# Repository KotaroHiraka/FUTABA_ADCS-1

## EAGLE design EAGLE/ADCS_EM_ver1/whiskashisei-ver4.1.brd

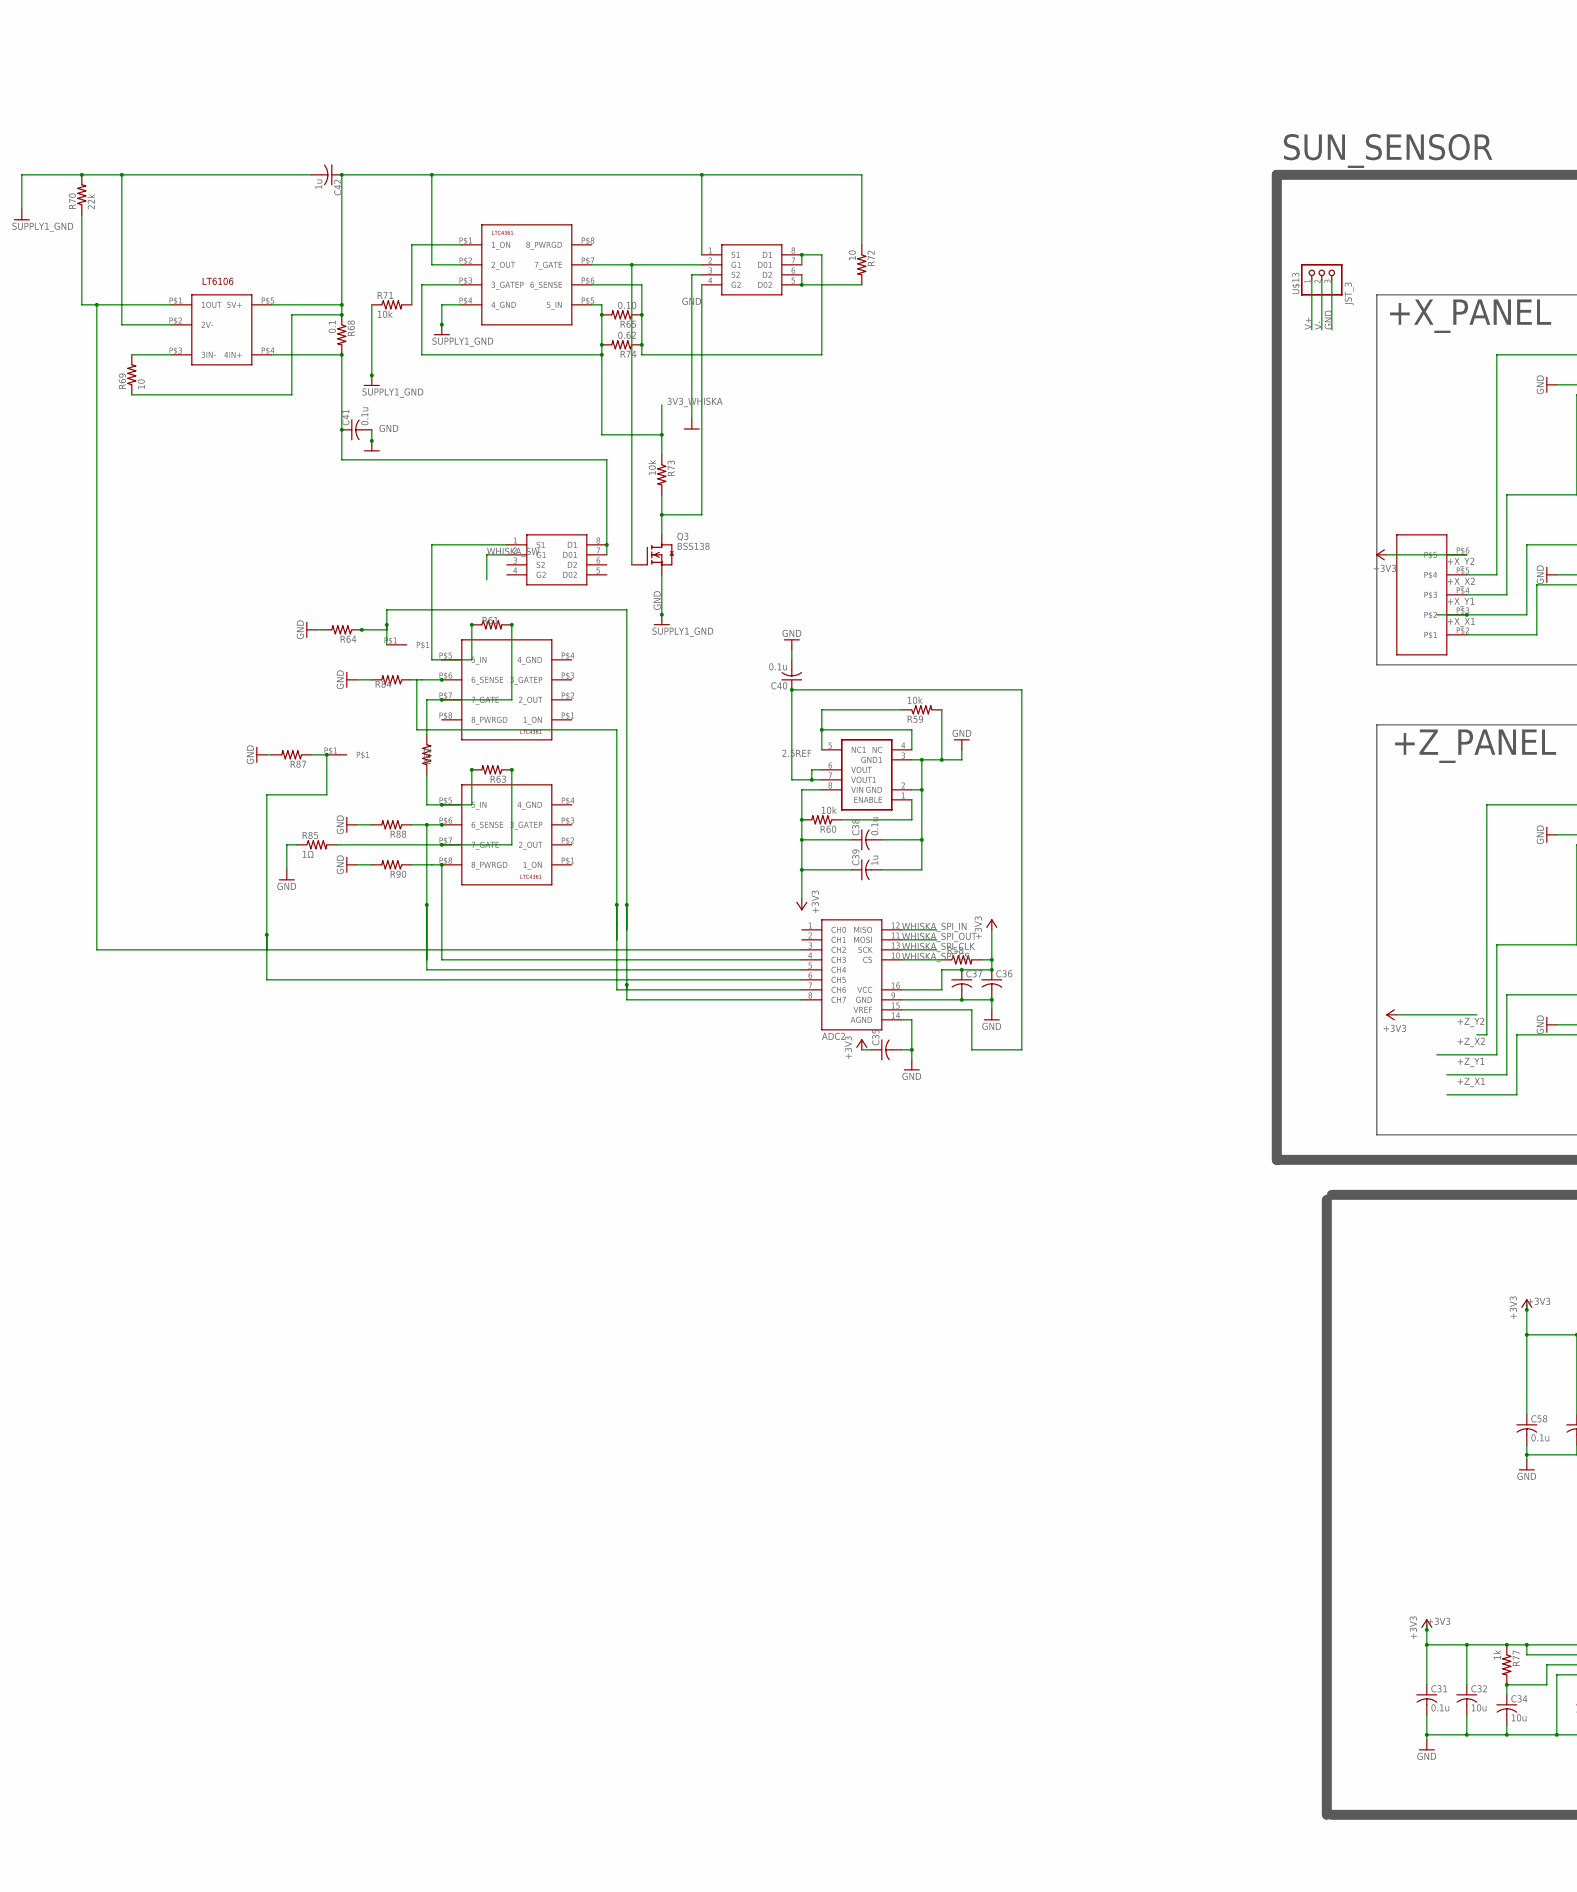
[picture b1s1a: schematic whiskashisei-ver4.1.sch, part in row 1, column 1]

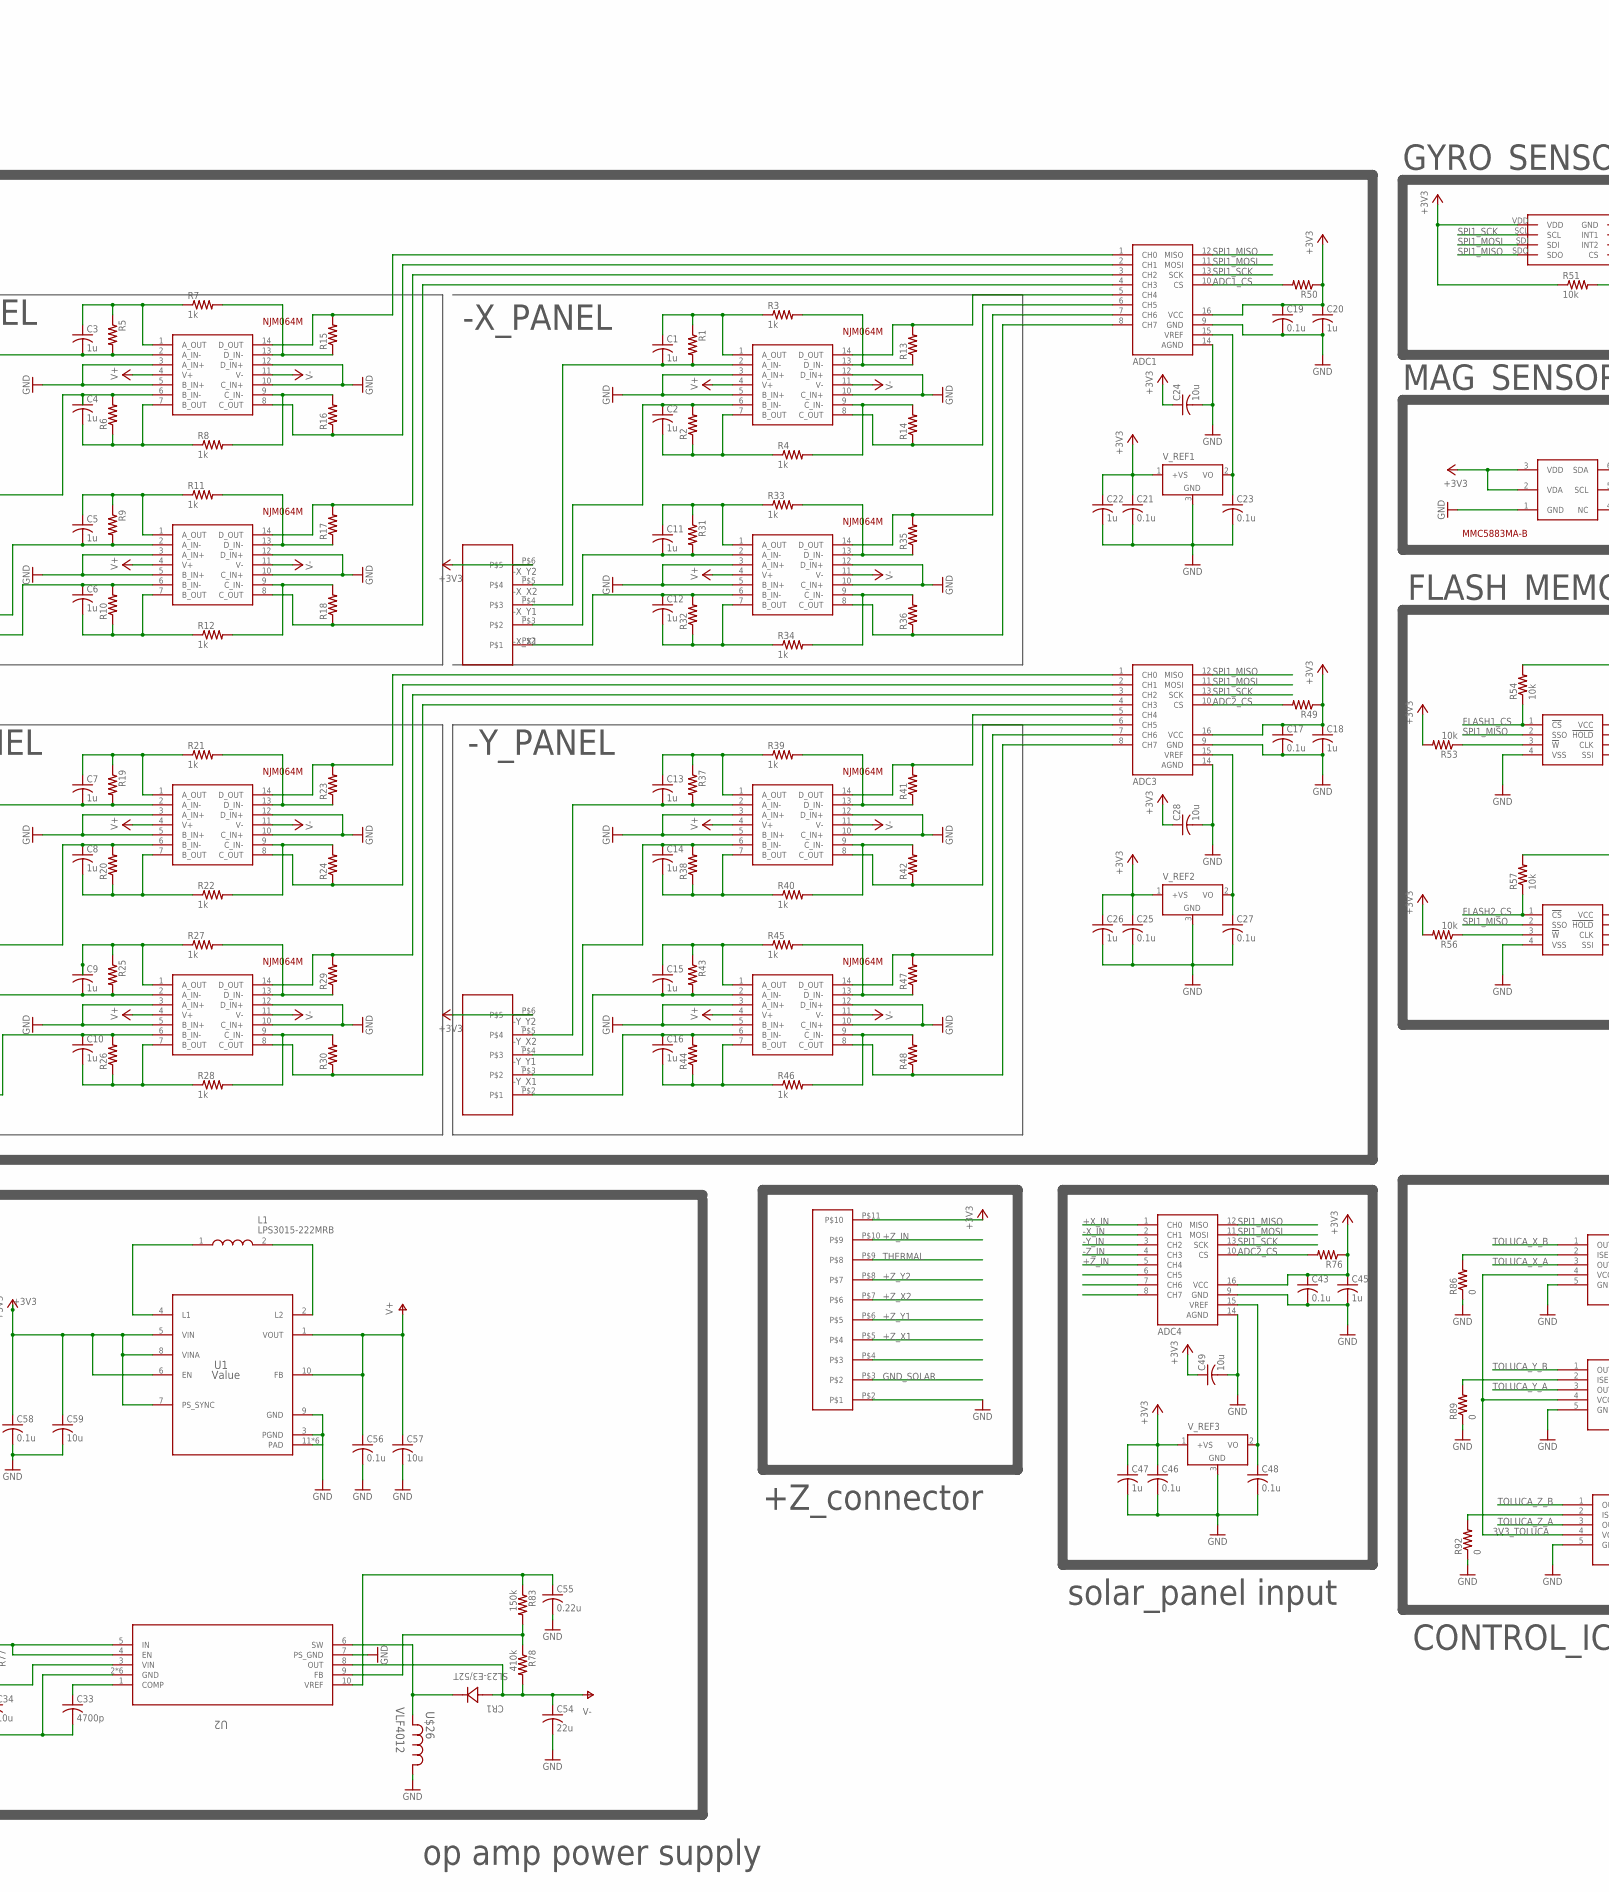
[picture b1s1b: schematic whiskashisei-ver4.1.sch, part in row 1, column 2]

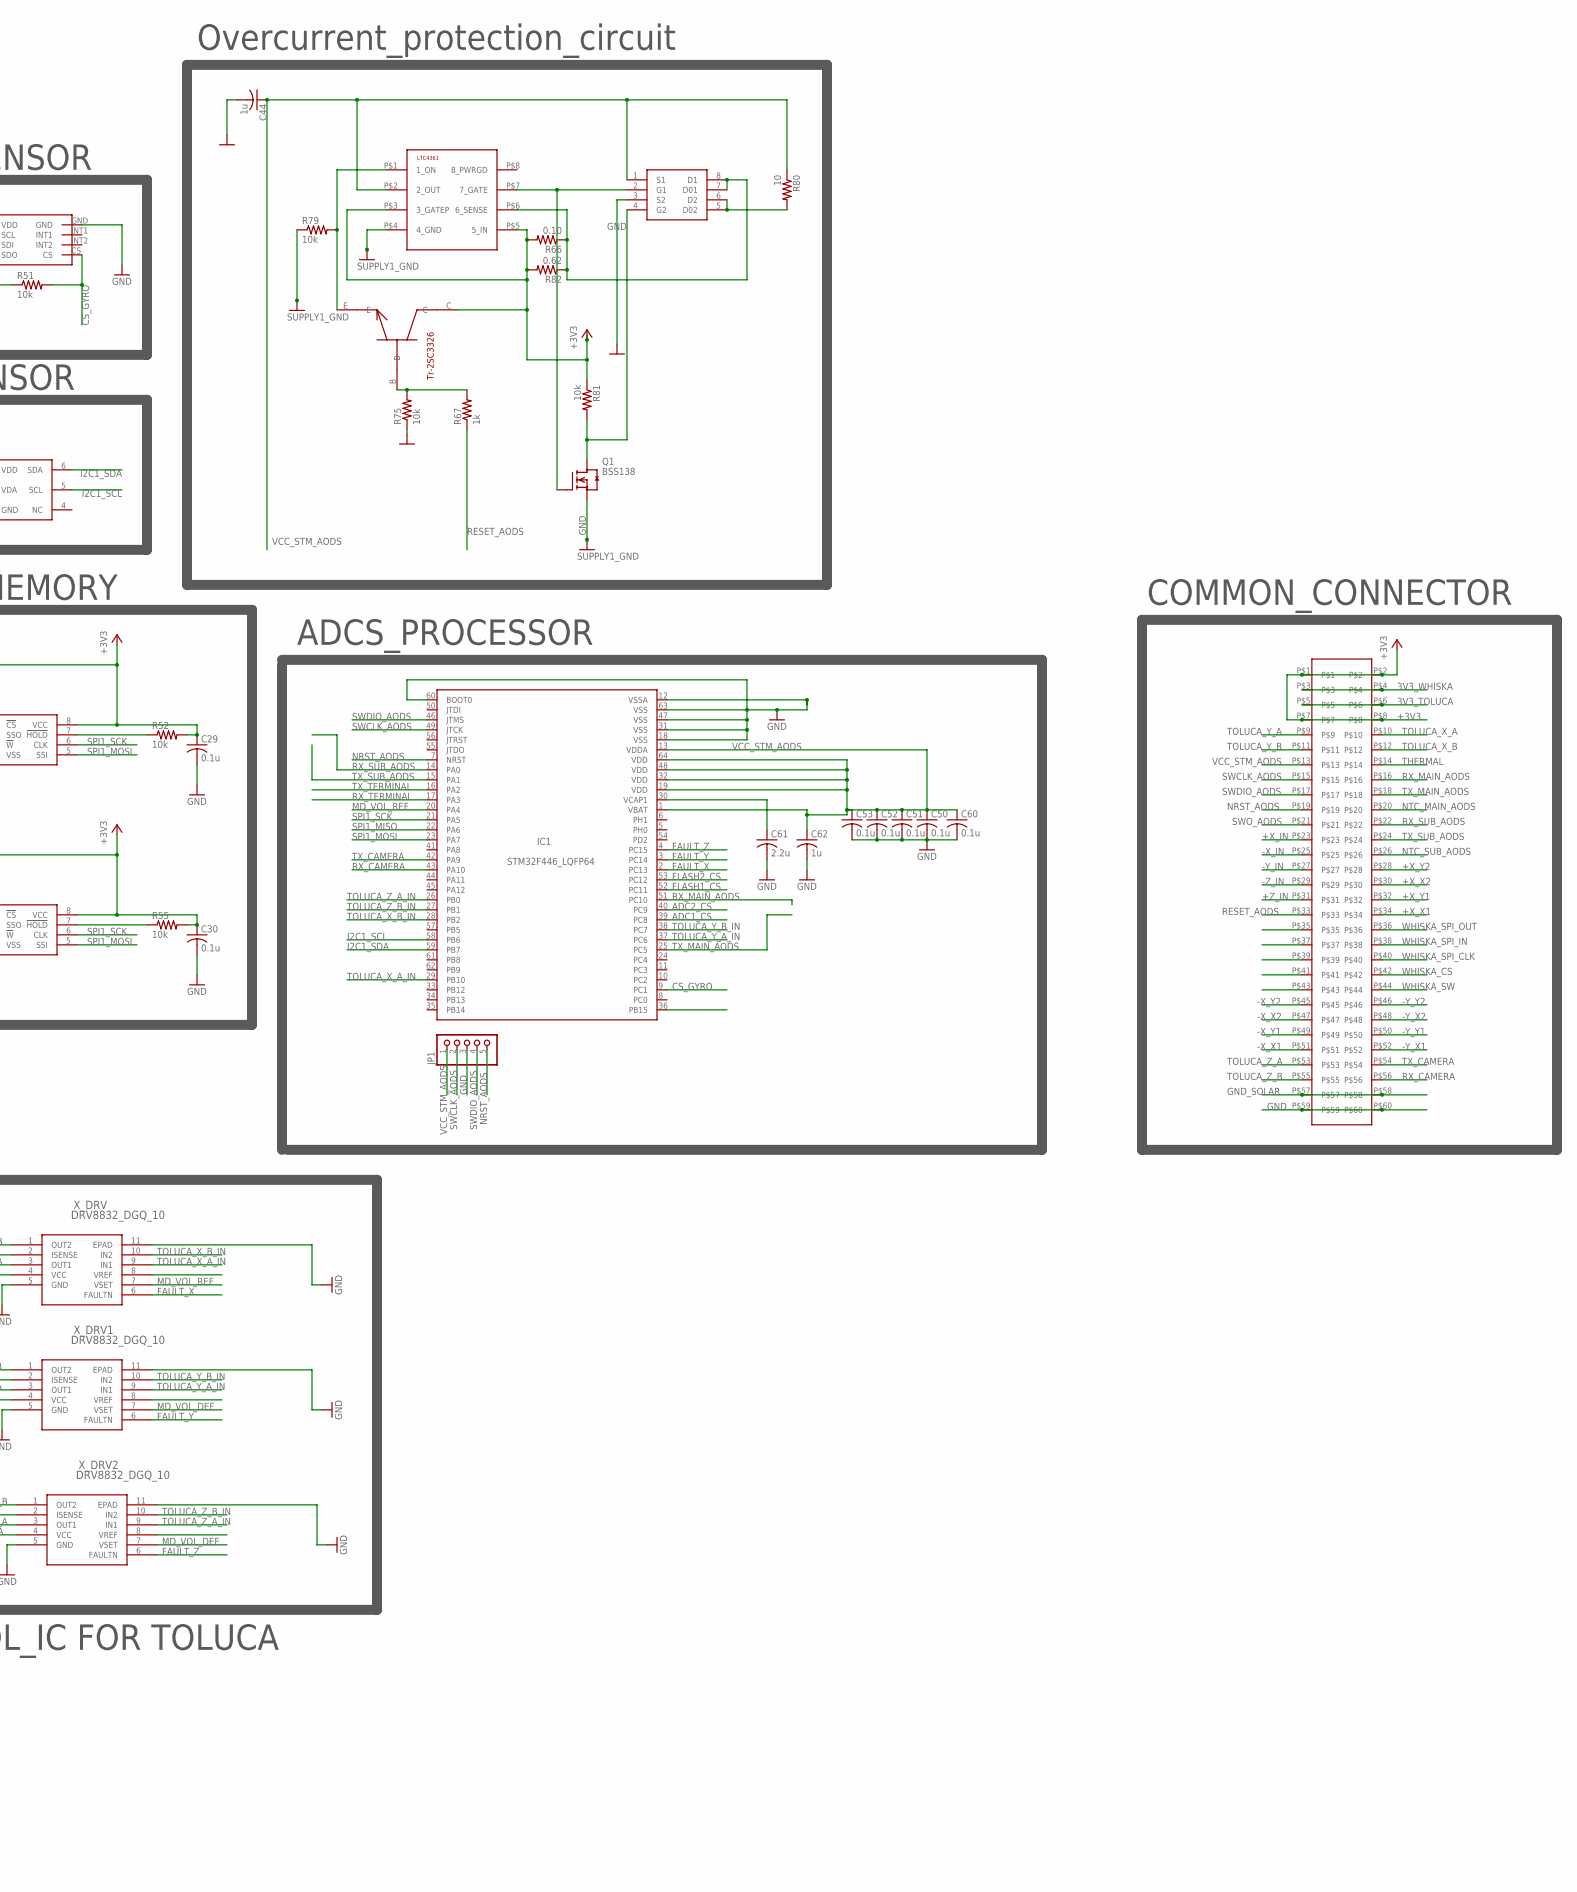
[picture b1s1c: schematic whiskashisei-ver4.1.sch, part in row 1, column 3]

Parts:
ADC1, ADC2, ADC3, ADC4: ADC_MCP3208; SO16
C1, C2, C3, C4, C5, C6, C7, C8, C9, C10, C11, C12, C13, C14, C15, C16, C18, C20, C22, C26, C39, C42, C44, C45, C47, C62: 1u; C2012
C17, C19, C21, C23, C25, C27, C29, C30, C31, C38, C40, C41, C43, C46, C48, C50, C51, C52, C53, C56, C58, C60: 0.1u; C2012
C24, C28, C32, C34, C49, C57, C59: 10u; C2012
C33: 4700p; C2012
C35, C36, C37: C-USC2012; C2012
C54: 22u; C2012
C55: 0.22u; C2012
C61: 2.2u; C2012
CR1: SL23-E3/52T; DIODE_DO214AA
FLASH_CAM: MP25P80; SO-08M
FLASH_SENSOR: MP25P80; SO-08M
IC1: STM32F446_LQFP64; LQFP64_PACKAGE
JP1: PINHD-1X5; 1X05
L1: LPS3015-222MRB; LPS3015
Q1, Q3: BSS138; SOT23
R1, R2, R5, R6, R9, R10, R13, R14, R15, R16, R17, R18, R19, R20, R23, R24, R25, R26, R29, R30, R31, R32, R35, R36, R37, R38, R41, R42, R43, R44, R47, R48, R49, R50, R58, R61, R62, R63, R64, R76, R84, R87, R88, R90: R-US_R2012; R2012
R3, R4, R7, R8, R11, R12, R21, R22, R27, R28, R33, R34, R39, R40, R45, R46, R67, R77: 1k; R2012
R51, R52, R53, R54, R55, R56, R57, R59, R60, R71, R73, R75, R79, R81: 10k; R2012
R65, R66: 0.10; R2012
R68: 0.1; R2012
R69, R72, R80: 10; R2012
R70: 22k; R2012
R74, R82: 0.62; R2012
R78: 410k; R2012
R83: 150k; R2012
R85: 1Ω; R2012
R86, R89, R92: 0; R2012
U1: Value; DRC0010A
U2: TPS63700DRCRG4; DRC10_2P4X1P65
U$1: 1.27_60
U$3: MMC5883MA-B
U$4: L3GD20_SET
U$5, U$6, U$7, U$8, U$9, U$10, U$11, U$12: NJM064M
U$13: JST_3
U$14: ADR3525
U$15, U$17, U$23, U$27: LTC4361; LTC4361_2
U$16, U$19, U$22: IRF7910; SO-08
U$18: LT6106
U$20: TR-NPN-2SC3326
U$21: JST_1MM_10
U$26: VLF4012; IND_4012
U$31, U$32, U$34: JST_1MM_5
V_REF1, V_REF2, V_REF3: LM50; SOT23
WHISKAPAD1, WHISKAPAD2: WHISKAPAD; LTC4361_2
X_DRV, X_DRV1, X_DRV2: DRV8832_DGQ_10; DGQ10_2P18X1P72

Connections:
2.5REF: ADC2.15 (VREF), C40.1, U$14.6 (VOUT), U$14.7 (VOUT1)
3V3_TOLUCA: U$1.P$5, U$1.P$6, X_DRV.4 (VCC), X_DRV1.4 (VCC), X_DRV2.4 (VCC)
3V3_WHISKA: R65.2, R73.1, R74.2, U$1.P$3, U$1.P$4, U$15.P$3 (3_GATEP), U$15.P$5 (5_IN)
+3V3: ADC1.16 (VCC), ADC2.16 (VCC), ADC3.16 (VCC), ADC4.16 (VCC), C17.1, C18.1, C19.1, C20.1, C21.1, C22.1, C24.1, C25.1, C26.1, C28.1, C29.1, C30.1, C31.1, C32.1, C35.1, C36.1, C37.1, C38.1, C39.1, C43.1, C45.1, C46.1, C47.1, C49.1, C58.1, C59.1, FLASH_CAM.8 (VCC), FLASH_SENSOR.8 (VCC), R49.1, R50.1, R51.1, R52.2, R53.2, R54.2, R55.2, R56.2, R57.2, R58.2, R60.2, R66.2, R76.1, R77.1, R81.1, R82.2, U1.5 (VIN), U1.6 (EN), U1.7 (PS_SYNC), U1.8 (VINA), U2.4 (EN), U2.5 (IN), U$1.P$1, U$1.P$2, U$1.P$7, U$1.P$8, U$3.2 (VDA), U$3.3 (VDD), U$4.VDD, U$14.8 (VIN), U$17.P$3 (3_GATEP), U$17.P$5 (5_IN), U$20.C, U$21.P$11, U$31.P$6, U$32.P$6, U$34.P$6, V_REF1.1 (+VS), V_REF2.1 (+VS), V_REF3.1 (+VS)
+X_IN: ADC4.1 (CH0), U$1.P$23
+X_X1: C6.1, R10.2, U$1.P$34, U$7.6 (B_IN-), U$31.P$2
+X_X2: C4.1, R6.2, U$1.P$30, U$6.6 (B_IN-), U$31.P$4
+X_Y1: C5.2, R9.2, U$1.P$32, U$7.2 (A_IN-), U$31.P$3
+X_Y2: C3.2, R5.2, U$1.P$28, U$6.2 (A_IN-), U$31.P$5
+Z_IN: ADC4.5 (CH4), U$1.P$31, U$21.P$10
+Z_X1: C10.1, R26.2, U$9.6 (B_IN-), U$21.P$5
+Z_X2: C8.1, R20.2, U$8.6 (B_IN-), U$21.P$7
+Z_Y1: C9.2, R25.2, U$9.2 (A_IN-), U$21.P$6
+Z_Y2: C7.2, R19.2, U$8.2 (A_IN-), U$21.P$8
-X_IN: ADC4.2 (CH1), U$1.P$25
-X_X1: C12.1, R32.2, U$1.P$51, U$10.6 (B_IN-), U$32.P$2
-X_X2: C2.1, R2.2, U$1.P$47, U$5.6 (B_IN-), U$32.P$4
-X_Y1: C11.2, R31.2, U$1.P$49, U$10.2 (A_IN-), U$32.P$3
-X_Y2: C1.2, R1.2, U$1.P$45, U$5.2 (A_IN-), U$32.P$5
-Y_IN: ADC4.3 (CH2), U$1.P$27
-Y_X1: C16.1, R44.2, U$1.P$52, U$12.6 (B_IN-), U$34.P$2
-Y_X2: C14.1, R38.2, U$1.P$48, U$11.6 (B_IN-), U$34.P$4
-Y_Y1: C15.2, R43.2, U$1.P$50, U$12.2 (A_IN-), U$34.P$3
-Y_Y2: C13.2, R37.2, U$1.P$46, U$11.2 (A_IN-), U$34.P$5
-Z_IN: ADC4.4 (CH3), U$1.P$29
ADC1_CS: ADC1.10 (CS), IC1.39 (PC8), R50.2
ADC2_CS: ADC3.10 (CS), ADC4.10 (CS), IC1.40 (PC9), R49.2, R76.2
CRT-18F: ADC2.3 (CH2), R70.1, U$18.P$1 (1OUT)
CS_GYRO: IC1.9 (PC1), R51.2, U$4.CS
FAULT_X: IC1.2 (PC13), X_DRV.6 (FAULTN)
FAULT_Y: IC1.3 (PC14), X_DRV1.6 (FAULTN)
FAULT_Z: IC1.4 (PC15), X_DRV2.6 (FAULTN)
FLASH1_CS: FLASH_SENSOR.1 (!CS), IC1.52 (PC11), R54.1
FLASH2_CS: FLASH_CAM.1 (!CS), IC1.53 (PC12), R57.1
G2: U$22.4 (G2)
GND: ADC1.9 (GND), ADC1.14 (AGND), ADC2.9 (GND), ADC2.14 (AGND), ADC3.9 (GND), ADC3.14 (AGND), ADC4.9 (GND), ADC4.14 (AGND), C17.2, C18.2, C19.2, C20.2, C21.2, C22.2, C23.2, C24.2, C25.2, C26.2, C27.2, C28.2, C29.2, C30.2, C31.2, C32.2, C33.2, C34.2, C35.2, C36.2, C37.2, C38.2, C39.2, C40.2, C41.2, C42.2, C43.2, C44.2, C45.2, C46.2, C47.2, C48.2, C49.2, C50.2, C51.2, C52.2, C53.2, C54.2, C55.2, C56.2, C57.2, C58.2, C59.2, C60.2, C61.2, C62.2, FLASH_CAM.4 (VSS), FLASH_SENSOR.4 (VSS), IC1.12 (VSSA), IC1.18 (VSS), IC1.31 (VSS), IC1.47 (VSS), IC1.60 (BOOT0), IC1.63 (VSS), JP1.3, Q1.2 (S), Q3.2 (S), R59.2, R64.2, R70.2, R71.1, R75.1, R79.1, R84.2, R85.1, R86.1, R87.2, R88.2, R89.1, R90.2, R92.1, U1.3 (PGND), U1.9 (GND), U1.11 (PAD), U1.P$1 (PAD), U1.P$2 (PAD), U1.P$3 (PAD), U1.P$4 (PAD), U1.V (PAD), U2.2 (GND), U2.7 (PS_GND), U2.11 (GND), U2.12 (GND), U2.13 (GND), U2.14 (GND), U2.15 (GND), U$1.P$59, U$1.P$60, U$3.1 (GND), U$4.GND, U$5.3 (A_IN+), U$5.5 (B_IN+), U$5.10 (C_IN+), U$5.12 (D_IN+), U$6.3 (A_IN+), U$6.5 (B_IN+), U$6.10 (C_IN+), U$6.12 (D_IN+), U$7.3 (A_IN+), U$7.5 (B_IN+), U$7.10 (C_IN+), U$7.12 (D_IN+), U$8.3 (A_IN+), U$8.5 (B_IN+), U$8.10 (C_IN+), U$8.12 (D_IN+), U$9.3 (A_IN+), U$9.5 (B_IN+), U$9.10 (C_IN+), U$9.12 (D_IN+), U$10.3 (A_IN+), U$10.5 (B_IN+), U$10.10 (C_IN+), U$10.12 (D_IN+), U$11.3 (A_IN+), U$11.5 (B_IN+), U$11.10 (C_IN+), U$11.12 (D_IN+), U$12.3 (A_IN+), U$12.5 (B_IN+), U$12.10 (C_IN+), U$12.12 (D_IN+), U$13.3, U$14.2 (GND), U$14.3 (GND1), U$15.P$4 (4_GND), U$16.3 (S2), U$17.P$4 (4_GND), U$18.P$2 (2V-), U$19.3 (S2), U$21.P$2, U$26.1, V_REF1.3 (GND), V_REF2.3 (GND), V_REF3.3 (GND), X_DRV.5 (GND), X_DRV.11 (EPAD), X_DRV1.5 (GND), X_DRV1.11 (EPAD), X_DRV2.5 (GND), X_DRV2.11 (EPAD)
GND_SOLAR: U$1.P$57, U$1.P$58, U$21.P$3
I2C1_SCL: IC1.58 (PB6), U$3.5 (SCL)
I2C1_SDA: IC1.59 (PB7), U$3.6 (SDA)
MD_VOL_DEF: X_DRV1.7 (VSET), X_DRV2.7 (VSET)
MD_VOL_REF: IC1.20 (PA4), X_DRV.7 (VSET)
unnamed: C4.2, R6.1, R8.1, U$6.7 (B_OUT)
unnamed: ADC1.1 (CH0), R15.2, U$6.14 (D_OUT)
unnamed: ADC1.2 (CH1), R16.1, U$6.8 (C_OUT)
unnamed: ADC1.6 (CH5), R14.1, U$5.8 (C_OUT)
unnamed: R8.2, R16.2, U$6.9 (C_IN-)
unnamed: ADC1.7 (CH6), R35.2, U$10.14 (D_OUT)
unnamed: ADC1.8 (CH7), R36.1, U$10.8 (C_OUT)
unnamed: ADC1.5 (CH4), R13.2, U$5.14 (D_OUT)
unnamed: ADC3.1 (CH0), R23.2, U$8.14 (D_OUT)
unnamed: C2.2, R2.1, R4.1, U$5.7 (B_OUT)
unnamed: R4.2, R14.2, U$5.9 (C_IN-)
unnamed: C8.2, R20.1, R22.1, U$8.7 (B_OUT)
unnamed: C1.1, R1.1, R3.1, U$5.1 (A_OUT)
unnamed: R3.2, R13.1, U$5.13 (D_IN-)
unnamed: C33.1, U2.1 (COMP)
unnamed: C3.1, R5.1, R7.1, U$6.1 (A_OUT)
unnamed: R7.2, R15.1, U$6.13 (D_IN-)
unnamed: C6.2, R10.1, R12.1, U$7.7 (B_OUT)
unnamed: R12.2, R18.2, U$7.9 (C_IN-)
unnamed: C5.1, R9.1, R11.1, U$7.1 (A_OUT)
unnamed: R11.2, R17.1, U$7.13 (D_IN-)
unnamed: R61.1, U$22.1 (S1), U$23.P$5 (5_IN)
unnamed: ADC1.15 (VREF), C23.1, V_REF1.2 (VO)
unnamed: ADC1.4 (CH3), R18.1, U$7.8 (C_OUT)
unnamed: C12.2, R32.1, R34.1, U$10.7 (B_OUT)
unnamed: ADC1.3 (CH2), R17.2, U$7.14 (D_OUT)
unnamed: R22.2, R24.2, U$8.9 (C_IN-)
unnamed: C7.1, R19.1, R21.1, U$8.1 (A_OUT)
unnamed: R21.2, R23.1, U$8.13 (D_IN-)
unnamed: C10.2, R26.1, R28.1, U$9.7 (B_OUT)
unnamed: R28.2, R30.2, U$9.9 (C_IN-)
unnamed: C9.1, R25.1, R27.1, U$9.1 (A_OUT)
unnamed: R27.2, R29.1, U$9.13 (D_IN-)
unnamed: C55.1, R83.1, U2.10 (VREF)
unnamed: C34.1, R77.2, U2.3 (VIN)
unnamed: ADC3.3 (CH2), R29.2, U$9.14 (D_OUT)
unnamed: ADC3.4 (CH3), R30.1, U$9.8 (C_OUT)
unnamed: R61.2, R62.2, U$23.P$7 (7_GATE)
unnamed: ADC3.2 (CH1), R24.1, U$8.8 (C_OUT)
unnamed: R34.2, R36.2, U$10.9 (C_IN-)
unnamed: C11.1, R31.1, R33.1, U$10.1 (A_OUT)
unnamed: R33.2, R35.1, U$10.13 (D_IN-)
unnamed: ADC3.15 (VREF), C27.1, V_REF2.2 (VO)
unnamed: ADC3.5 (CH4), R41.2, U$11.14 (D_OUT)
unnamed: ADC3.6 (CH5), R42.1, U$11.8 (C_OUT)
unnamed: C14.2, R38.1, R40.1, U$11.7 (B_OUT)
unnamed: R40.2, R42.2, U$11.9 (C_IN-)
unnamed: C13.1, R37.1, R39.1, U$11.1 (A_OUT)
unnamed: R39.2, R41.1, U$11.13 (D_IN-)
unnamed: ADC4.15 (VREF), C48.1, V_REF3.2 (VO)
unnamed: C16.2, R44.1, R46.1, U$12.7 (B_OUT)
unnamed: R46.2, R48.2, U$12.9 (C_IN-)
unnamed: C15.1, R43.1, R45.1, U$12.1 (A_OUT)
unnamed: R45.2, R47.1, U$12.13 (D_IN-)
unnamed: R78.1, R83.2, U2.9 (FB)
unnamed: CR1.1, U2.6 (SW), U$26.2
unnamed: ADC3.7 (CH6), R47.2, U$12.14 (D_OUT)
unnamed: ADC3.8 (CH7), R48.1, U$12.8 (C_OUT)
unnamed: R65.1, R74.1, U$15.P$6 (6_SENSE), U$16.7 (D01), U$16.8 (D1)
unnamed: FLASH_SENSOR.3 (!W), R53.1
unnamed: FLASH_CAM.7 (!HOLD), R55.1
unnamed: Q3.1 (G), U$15.P$7 (7_GATE), U$16.2 (G1)
unnamed: FLASH_CAM.3 (!W), R56.1
unnamed: FLASH_SENSOR.7 (!HOLD), R52.1
unnamed: C42.1, R68.1, R69.1, R72.1, U$15.P$2 (2_OUT), U$16.1 (S1), U$18.P$5 (5V+)
unnamed: R89.2, X_DRV1.2 (ISENSE)
unnamed: R62.1, R63.2, U$27.P$5 (5_IN)
unnamed: L1.1, U1.4 (L1)
unnamed: L1.2, U1.2 (L2)
unnamed: R59.1, U$14.4 (NC), U$14.5 (NC1)
unnamed: R60.1, U$14.1 (ENABLE)
unnamed: R71.2, U$15.P$1 (1_ON)
unnamed: C41.1, R68.2, U$18.P$4 (4IN+), U$22.7 (D01), U$22.8 (D1)
unnamed: R69.2, U$18.P$3 (3IN-)
unnamed: R72.2, U$16.5 (D02), U$16.6 (D2)
unnamed: Q3.3 (D), R73.2, U$16.4 (G2)
unnamed: R66.1, R82.1, U$17.P$6 (6_SENSE), U$19.7 (D01), U$19.8 (D1)
unnamed: Q1.1 (G), U$17.P$7 (7_GATE), U$19.2 (G1)
unnamed: R79.2, U$17.P$1 (1_ON), U$20.E
unnamed: R67.2, R75.2, U$20.B
unnamed: R80.2, U$19.5 (D02), U$19.6 (D2)
unnamed: Q1.3 (D), R81.2, U$19.4 (G2)
unnamed: R92.2, X_DRV2.2 (ISENSE)
unnamed: ADC2.6 (CH5), R87.1, WHISKAPAD1.P$1
unnamed: ADC2.4 (CH3), R90.1, U$27.P$8 (8_PWRGD)
unnamed: ADC2.5 (CH4), R88.1, U$27.P$6 (6_SENSE)
unnamed: R86.2, X_DRV.2 (ISENSE)
unnamed: R63.1, R85.2, U$27.P$7 (7_GATE)
unnamed: ADC2.8 (CH7), R64.1, WHISKAPAD2.P$1
unnamed: ADC2.7 (CH6), R84.1, U$23.P$6 (6_SENSE)
unnamed: C61.1, IC1.30 (VCAP1)
NRST_AODS: IC1.7 (NRST), JP1.5, U$1.P$19
NTC_MAIN_AODS: U$1.P$20
NTC_SUB_AODS: U$1.P$26
RESET_AODS: R67.1, U$1.P$33
RX_CAMERA: IC1.43 (PA10), U$1.P$56
RX_MAIN_AODS: IC1.51 (PC10), U$1.P$16
RX_SUB_AODS: IC1.14 (PA0), U$1.P$22
RX_TERMINAL: IC1.17 (PA3)
SPI1_MISO: ADC1.12 (MISO), ADC3.12 (MISO), ADC4.12 (MISO), FLASH_CAM.2 (SSO), FLASH_SENSOR.2 (SSO), IC1.22 (PA6), U$4.SDO
SPI1_MOSI: ADC1.11 (MOSI), ADC3.11 (MOSI), ADC4.11 (MOSI), FLASH_CAM.5 (SSI), FLASH_SENSOR.5 (SSI), IC1.23 (PA7), U$4.SDI
SPI1_SCK: ADC1.13 (SCK), ADC3.13 (SCK), ADC4.13 (SCK), FLASH_CAM.6 (CLK), FLASH_SENSOR.6 (CLK), IC1.21 (PA5), U$4.SCL
SWCLK_AODS: IC1.49 (JTCK), JP1.2, U$1.P$15
SWDIO_AODS: IC1.46 (JTMS), JP1.4, U$1.P$17
SWO_AODS: U$1.P$21
THERMAL: U$1.P$14, U$21.P$9
TOLUCA_X_A: U$1.P$10, X_DRV.3 (OUT1)
TOLUCA_X_A_IN: IC1.29 (PB10), X_DRV.9 (IN1)
TOLUCA_X_B: U$1.P$12, X_DRV.1 (OUT2)
TOLUCA_X_B_IN: IC1.28 (PB2), X_DRV.10 (IN2)
TOLUCA_Y_A: U$1.P$9, X_DRV1.3 (OUT1)
TOLUCA_Y_A_IN: IC1.37 (PC6), X_DRV1.9 (IN1)
TOLUCA_Y_B: U$1.P$11, X_DRV1.1 (OUT2)
TOLUCA_Y_B_IN: IC1.38 (PC7), X_DRV1.10 (IN2)
TOLUCA_Z_A: U$1.P$53, X_DRV2.3 (OUT1)
TOLUCA_Z_A_IN: IC1.26 (PB0), X_DRV2.9 (IN1)
TOLUCA_Z_B: U$1.P$55, X_DRV2.1 (OUT2)
TOLUCA_Z_B_IN: IC1.27 (PB1), X_DRV2.10 (IN2)
TX_CAMERA: IC1.42 (PA9), U$1.P$54
TX_MAIN_AODS: IC1.25 (PC5), U$1.P$18
TX_SUB_AODS: IC1.15 (PA1), U$1.P$24
TX_TERMINAL: IC1.16 (PA2)
V+: C56.1, C57.1, U1.1 (VOUT), U1.10 (FB), U$5.4 (V+), U$6.4 (V+), U$7.4 (V+), U$8.4 (V+), U$9.4 (V+), U$10.4 (V+), U$11.4 (V+), U$12.4 (V+), U$13.1
V-: C54.1, CR1.2, R78.2, U2.8 (OUT), U$5.11 (V-), U$6.11 (V-), U$7.11 (V-), U$8.11 (V-), U$9.11 (V-), U$10.11 (V-), U$11.11 (V-), U$12.11 (V-), U$13.2
VCC_STM_AODS: C44.1, C50.1, C51.1, C52.1, C53.1, C60.1, C62.1, IC1.1 (VBAT), IC1.13 (VDDA), IC1.19 (VDD), IC1.32 (VDD), IC1.48 (VDD), IC1.64 (VDD), JP1.1, R80.1, U$1.P$13, U$17.P$2 (2_OUT), U$19.1 (S1)
WHISKA_CS: U$1.P$42
WHISKA_SPI_CLK: ADC2.13 (SCK), U$1.P$40
WHISKA_SPI_CS: ADC2.10 (CS), R58.1
WHISKA_SPI_IN: ADC2.12 (MISO), U$1.P$38
WHISKA_SPI_OUT: ADC2.11 (MOSI), U$1.P$36
WHISKA_SW: U$1.P$44, U$22.2 (G1)

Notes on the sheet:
+X_PANEL
-X_PANEL
+Z_PANEL
-Y_PANEL
SUN_SENSOR
GYRO_SENSOR
MAG_SENSOR
FLASH_MEMORY
+Z_connector
solar_panel input
op amp power supply
Overcurrent_protection_circuit
COMMON_CONNECTOR
ADCS_PROCESSOR
CONTROL_IC FOR TOLUCA

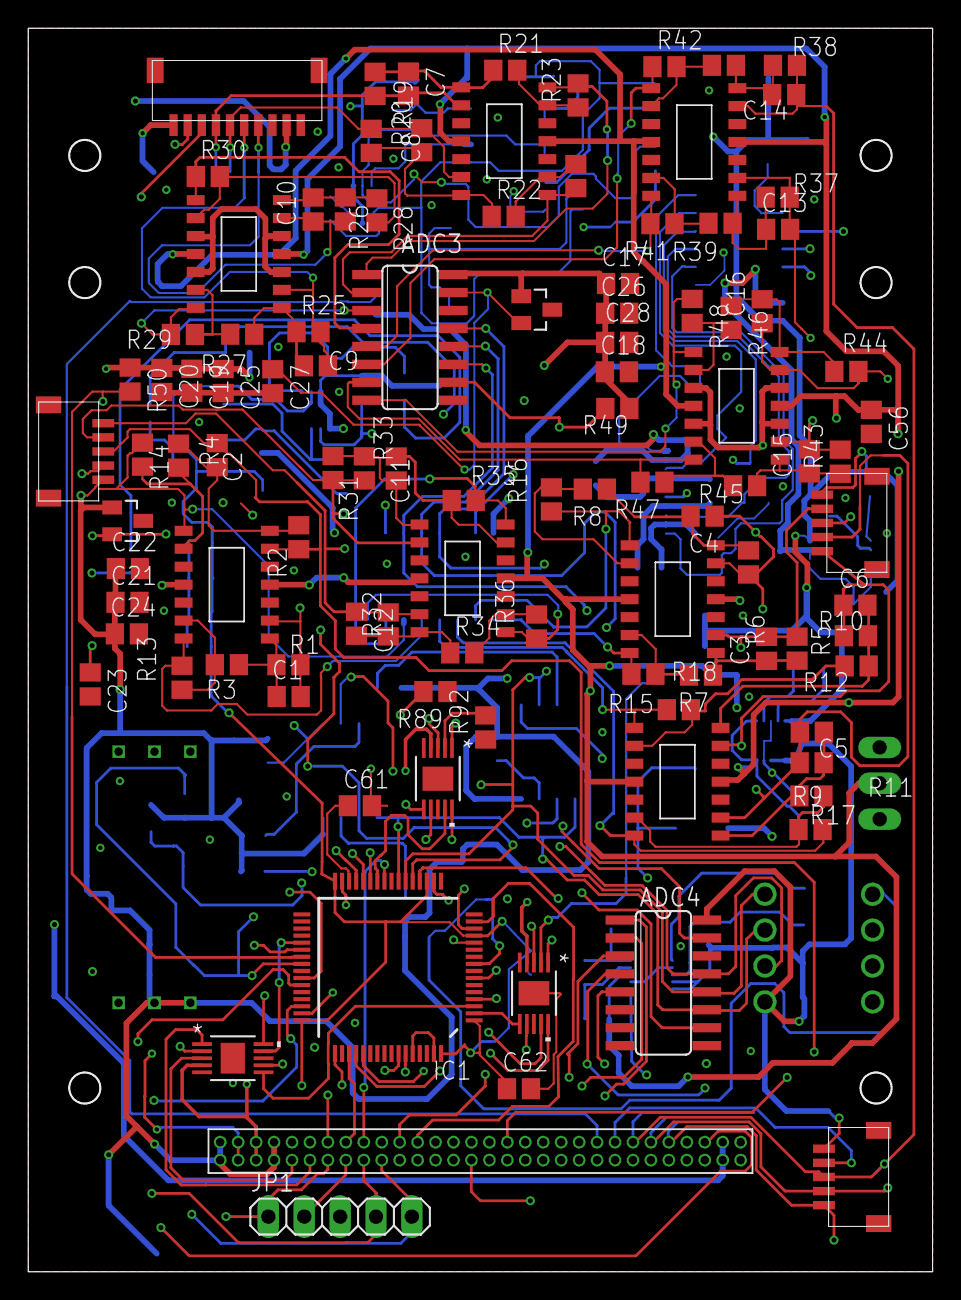
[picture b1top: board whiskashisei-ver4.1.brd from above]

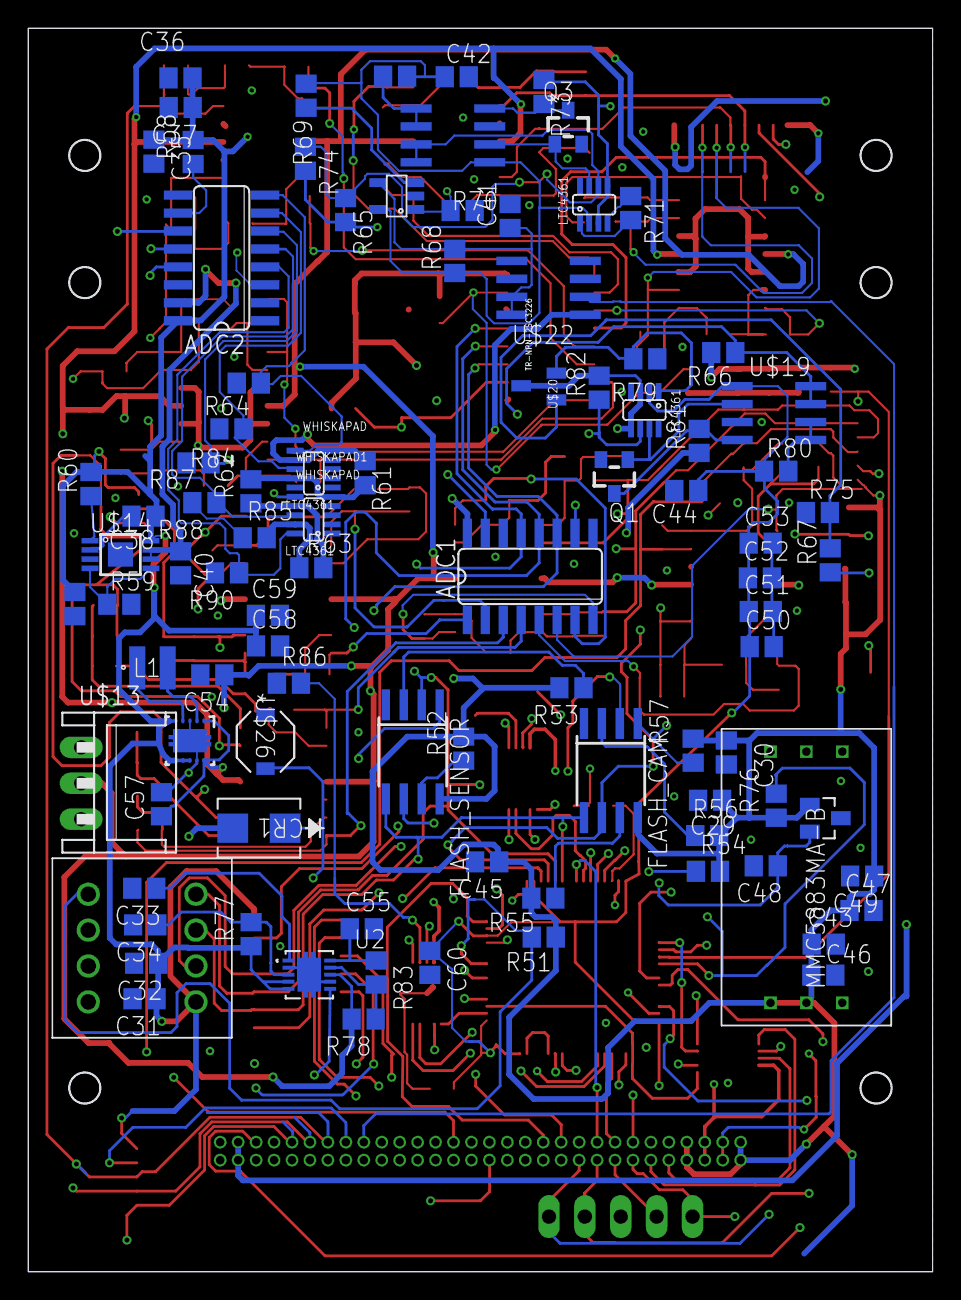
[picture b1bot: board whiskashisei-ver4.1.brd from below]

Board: 4 copper layers, 64.0 x 88.0 mm, 202 parts (97 on the bottom side), 165 nets.

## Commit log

2019-07-02 Create gyro_CRM_test
2019-07-02 ジャイロと通信できるようになった
2019-07-03 動作確認済
2019-07-03 create library
    ライブラリ化
    受信データのchecksum計算は未実装
2019-07-11 データを連続出力するようにした
2019-07-15 標準出力先を追加
2019-07-16 Add EAGLE EM_ver1
2019-07-18 Add Lecture
2019-07-20 サンプリングレートを50Hzに固定
